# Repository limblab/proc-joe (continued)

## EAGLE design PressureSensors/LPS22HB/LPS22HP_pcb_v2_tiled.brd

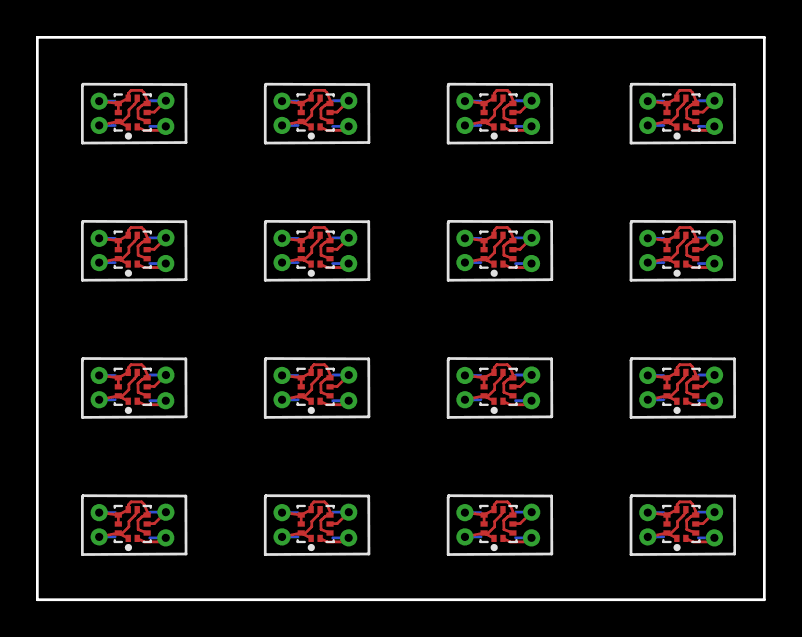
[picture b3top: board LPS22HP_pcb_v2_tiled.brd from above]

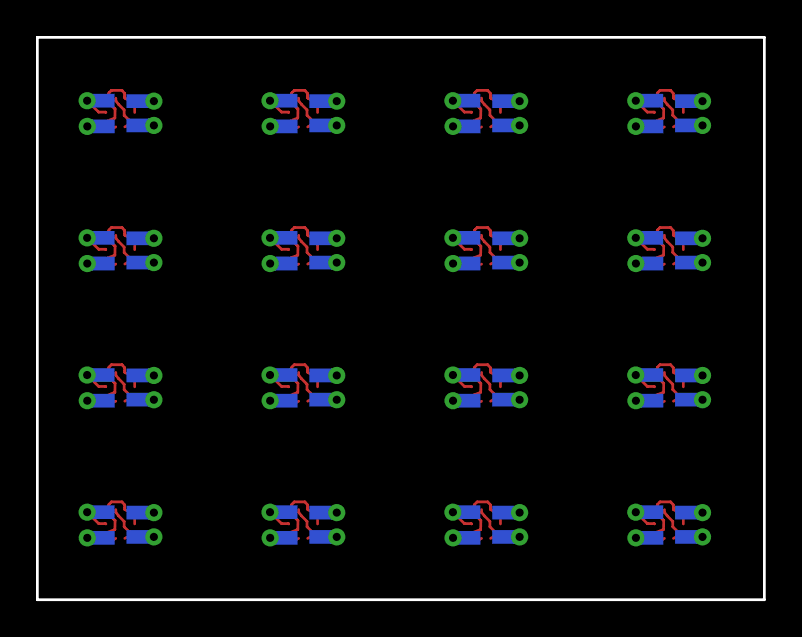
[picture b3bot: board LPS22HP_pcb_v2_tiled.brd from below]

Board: 2 copper layers, 40.4 x 31.2 mm, 80 parts (64 on the bottom side), 64 nets.

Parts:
U1, U2, U3, U4, U5, U6, U7, U8, U9, U10, U11, U12, U13, U14, U15, U16: LPS22HB; LGA10R50P2X3_200X200X80
U$1, U$2, U$3, U$4, U$5, U$6, U$7, U$8, U$9, U$10, U$11, U$12, U$13, U$14, U$15, U$16, U$17, U$18, U$19, U$20, U$21, U$22, U$23, U$24, U$25, U$26, U$27, U$28, U$29, U$30, U$31, U$32, U$33, U$34, U$35, U$36, U$37, U$38, U$39, U$40, U$41, U$42, U$43, U$44, U$45, U$46, U$47, U$48, U$49, U$50, U$51, U$52, U$53, U$54, U$55, U$56, U$57, U$58, U$59, U$60, U$61, U$62, U$63, U$64: WIREPAD_PADWIREPAD_0,6/0,4_PAD; WIREPAD_0,6/0,4_PAD

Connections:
+3V1: U2.1, U2.6, U2.10, U$5.P$1, U$5.P$2
+3V2: U3.1, U3.6, U3.10, U$11.P$1, U$11.P$2
+3V3: U1.1, U1.6, U1.10, U$1.P$1, U$1.P$2
+3V4: U4.1, U4.6, U4.10, U$15.P$1, U$15.P$2
+3V5: U5.1, U5.6, U5.10, U$19.P$1, U$19.P$2
+3V6: U6.1, U6.6, U6.10, U$23.P$1, U$23.P$2
+3V7: U7.1, U7.6, U7.10, U$27.P$1, U$27.P$2
+3V8: U8.1, U8.6, U8.10, U$31.P$1, U$31.P$2
+3V9: U9.1, U9.6, U9.10, U$35.P$1, U$35.P$2
+3V10: U10.1, U10.6, U10.10, U$39.P$1, U$39.P$2
+3V11: U11.1, U11.6, U11.10, U$43.P$1, U$43.P$2
+3V12: U12.1, U12.6, U12.10, U$47.P$1, U$47.P$2
+3V13: U13.1, U13.6, U13.10, U$51.P$1, U$51.P$2
+3V14: U14.1, U14.6, U14.10, U$55.P$1, U$55.P$2
+3V15: U15.1, U15.6, U15.10, U$59.P$1, U$59.P$2
+3V16: U16.1, U16.6, U16.10, U$63.P$1, U$63.P$2
GND: U1.3, U1.5, U1.7, U1.8, U1.9, U$2.P$1, U$2.P$2
GND1: U2.3, U2.5, U2.7, U2.8, U2.9, U$8.P$1, U$8.P$2
GND2: U3.3, U3.5, U3.7, U3.8, U3.9, U$12.P$1, U$12.P$2
GND3: U4.3, U4.5, U4.7, U4.8, U4.9, U$16.P$1, U$16.P$2
GND4: U5.3, U5.5, U5.7, U5.8, U5.9, U$20.P$1, U$20.P$2
GND5: U6.3, U6.5, U6.7, U6.8, U6.9, U$24.P$1, U$24.P$2
GND6: U7.3, U7.5, U7.7, U7.8, U7.9, U$28.P$1, U$28.P$2
GND7: U8.3, U8.5, U8.7, U8.8, U8.9, U$32.P$1, U$32.P$2
GND8: U9.3, U9.5, U9.7, U9.8, U9.9, U$36.P$1, U$36.P$2
GND9: U10.3, U10.5, U10.7, U10.8, U10.9, U$40.P$1, U$40.P$2
GND10: U11.3, U11.5, U11.7, U11.8, U11.9, U$44.P$1, U$44.P$2
GND11: U12.3, U12.5, U12.7, U12.8, U12.9, U$48.P$1, U$48.P$2
GND12: U13.3, U13.5, U13.7, U13.8, U13.9, U$52.P$1, U$52.P$2
GND13: U14.3, U14.5, U14.7, U14.8, U14.9, U$56.P$1, U$56.P$2
GND14: U15.3, U15.5, U15.7, U15.8, U15.9, U$60.P$1, U$60.P$2
GND15: U16.3, U16.5, U16.7, U16.8, U16.9, U$64.P$1, U$64.P$2
unnamed: U2.2, U$3.P$1, U$3.P$2
unnamed: U1.2, U$6.P$1, U$6.P$2
unnamed: U1.4, U$7.P$1, U$7.P$2
unnamed: U2.4, U$4.P$1, U$4.P$2
unnamed: U3.2, U$9.P$1, U$9.P$2
unnamed: U3.4, U$10.P$1, U$10.P$2
unnamed: U4.2, U$13.P$1, U$13.P$2
unnamed: U4.4, U$14.P$1, U$14.P$2
unnamed: U5.2, U$17.P$1, U$17.P$2
unnamed: U5.4, U$18.P$1, U$18.P$2
unnamed: U6.2, U$21.P$1, U$21.P$2
unnamed: U6.4, U$22.P$1, U$22.P$2
unnamed: U7.2, U$25.P$1, U$25.P$2
unnamed: U7.4, U$26.P$1, U$26.P$2
unnamed: U8.2, U$29.P$1, U$29.P$2
unnamed: U8.4, U$30.P$1, U$30.P$2
unnamed: U9.2, U$33.P$1, U$33.P$2
unnamed: U9.4, U$34.P$1, U$34.P$2
unnamed: U10.2, U$37.P$1, U$37.P$2
unnamed: U10.4, U$38.P$1, U$38.P$2
unnamed: U11.2, U$41.P$1, U$41.P$2
unnamed: U11.4, U$42.P$1, U$42.P$2
unnamed: U12.2, U$45.P$1, U$45.P$2
unnamed: U12.4, U$46.P$1, U$46.P$2
unnamed: U13.2, U$49.P$1, U$49.P$2
unnamed: U13.4, U$50.P$1, U$50.P$2
unnamed: U14.2, U$53.P$1, U$53.P$2
unnamed: U14.4, U$54.P$1, U$54.P$2
unnamed: U15.2, U$57.P$1, U$57.P$2
unnamed: U15.4, U$58.P$1, U$58.P$2
unnamed: U16.2, U$61.P$1, U$61.P$2
unnamed: U16.4, U$62.P$1, U$62.P$2

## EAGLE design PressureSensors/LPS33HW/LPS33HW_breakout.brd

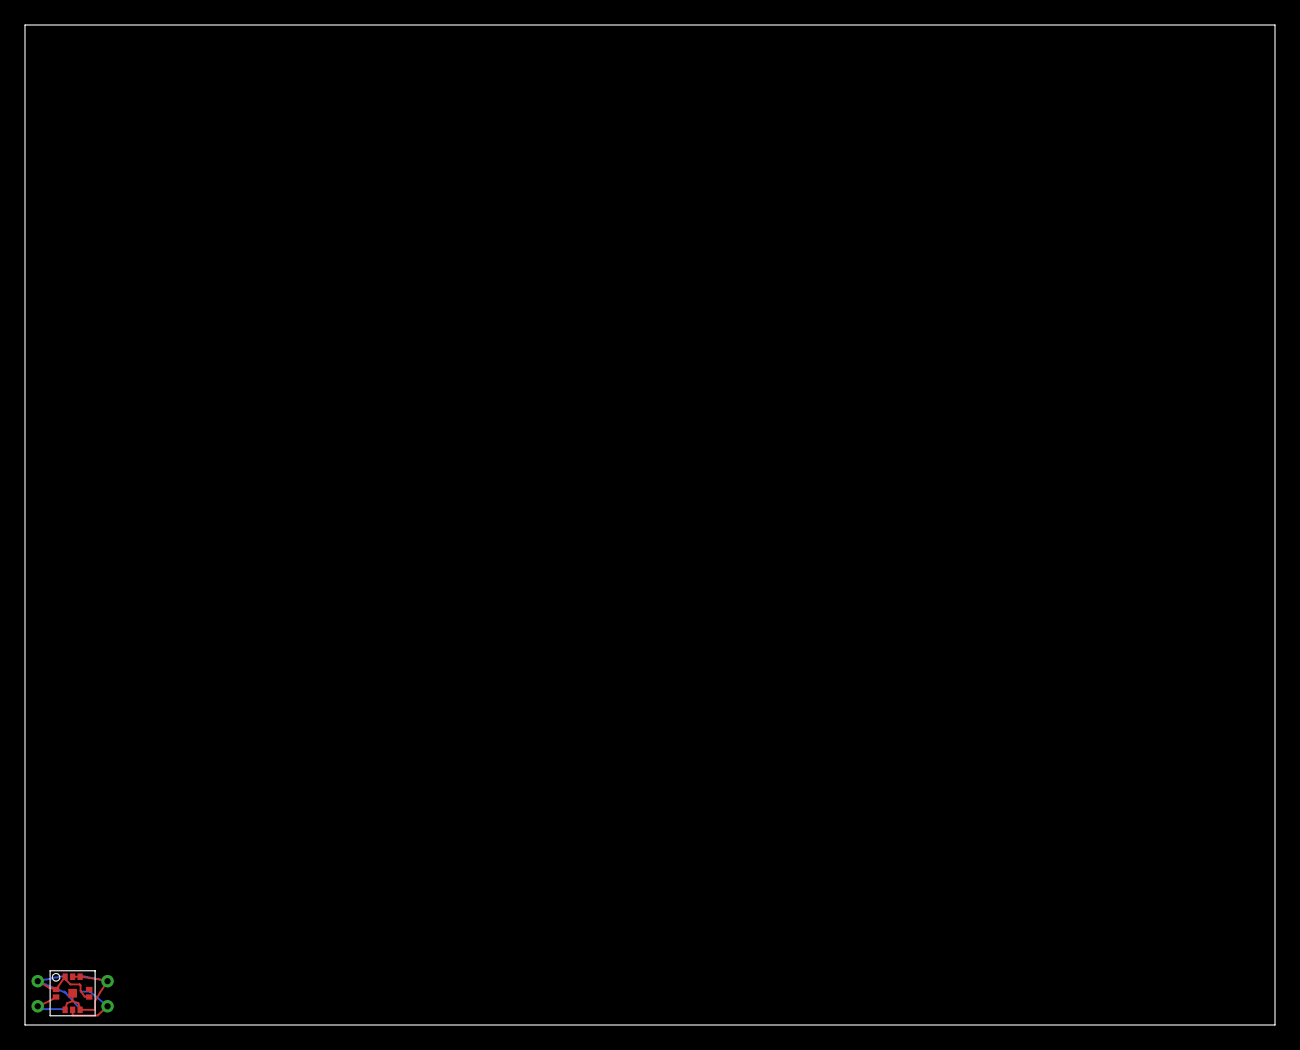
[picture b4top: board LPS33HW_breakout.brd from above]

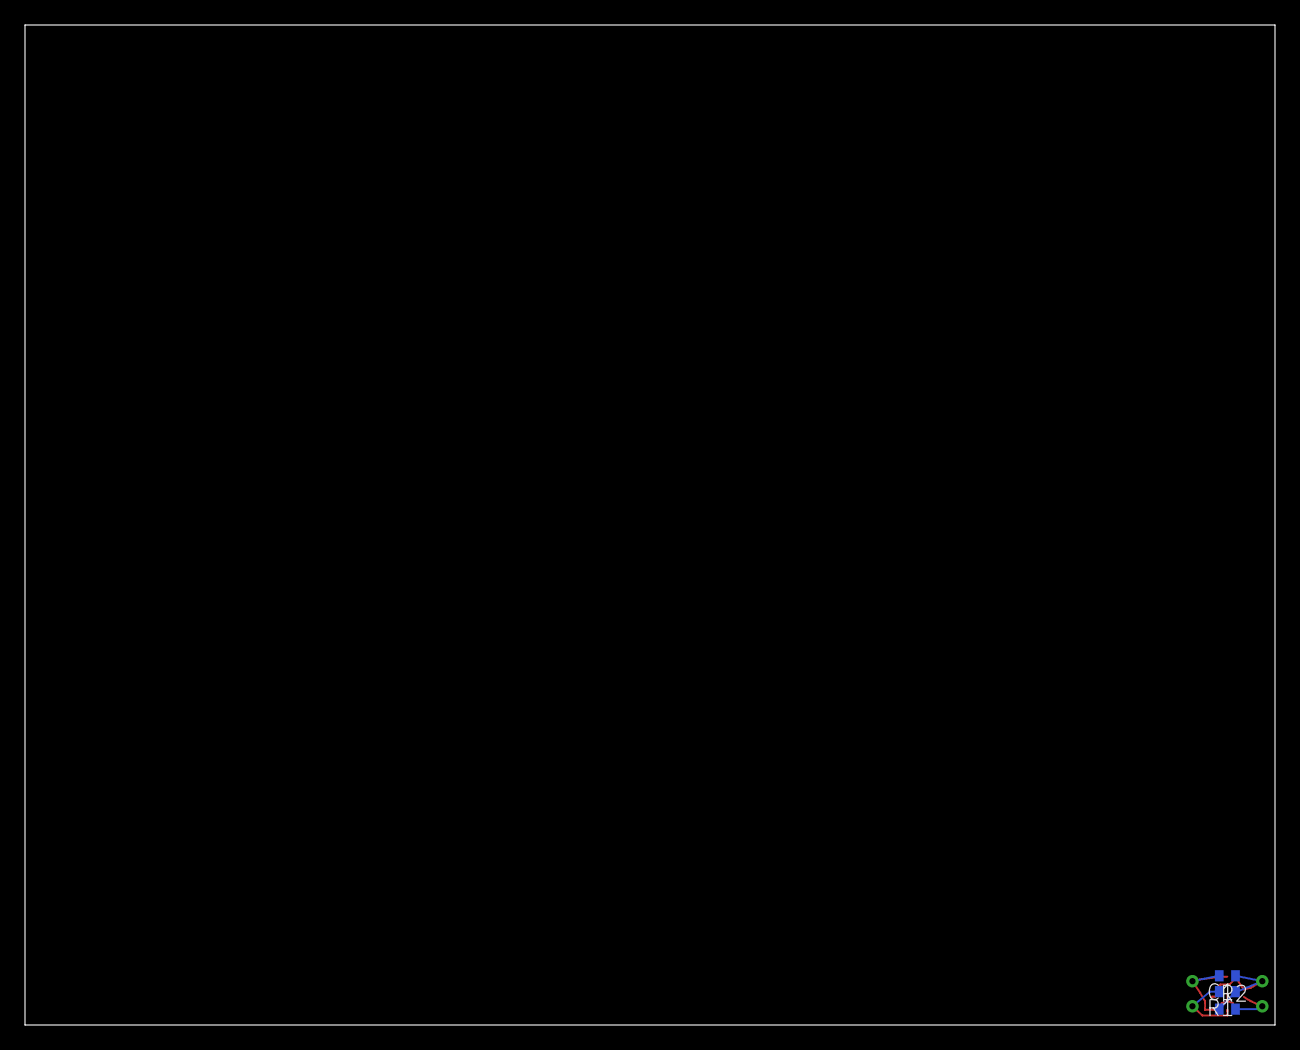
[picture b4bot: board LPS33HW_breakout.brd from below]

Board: 2 copper layers, 100.0 x 80.0 mm, 8 parts (3 on the bottom side), 4 nets.

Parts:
C1: C0402
R1, R2: R0402
U$1: LPS33HW
U$2, U$3, U$4, U$5: VIA

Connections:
+3V3: C1.1, R1.1, R2.1, U$1.P$1, U$1.P$6, U$1.P$10, U$2.P$1
GND: C1.2, U$1.GND, U$1.P$3, U$1.P$5, U$1.P$8, U$1.P$9, U$3.P$1
unnamed: R2.2, U$1.P$2, U$5.P$1
unnamed: R1.2, U$1.P$4, U$4.P$1

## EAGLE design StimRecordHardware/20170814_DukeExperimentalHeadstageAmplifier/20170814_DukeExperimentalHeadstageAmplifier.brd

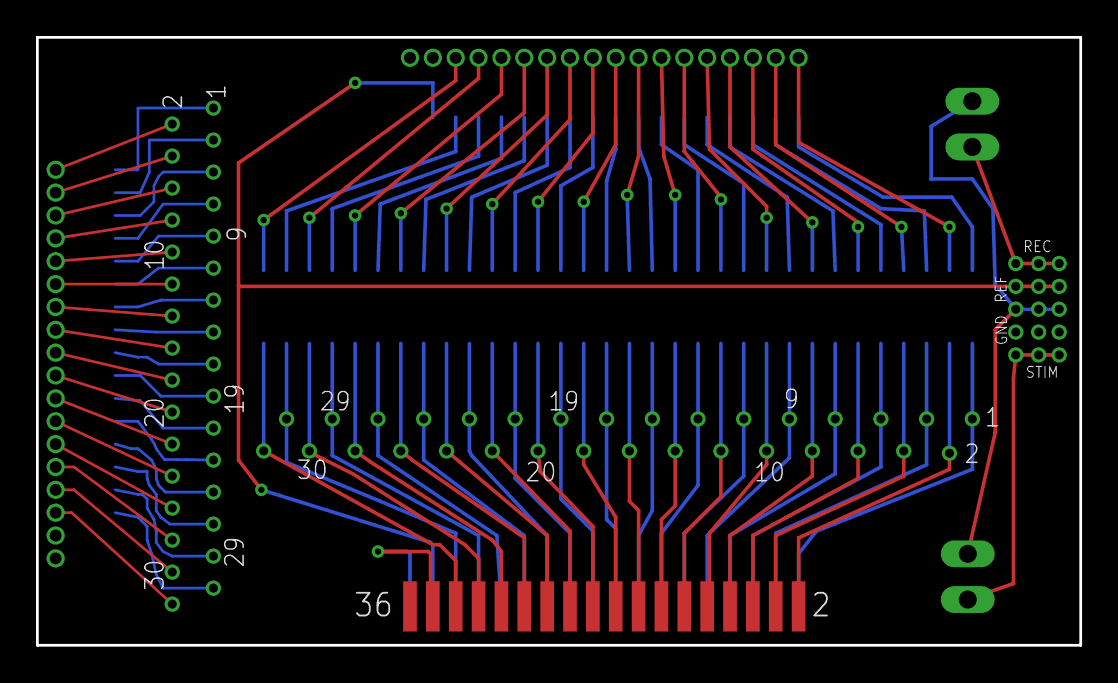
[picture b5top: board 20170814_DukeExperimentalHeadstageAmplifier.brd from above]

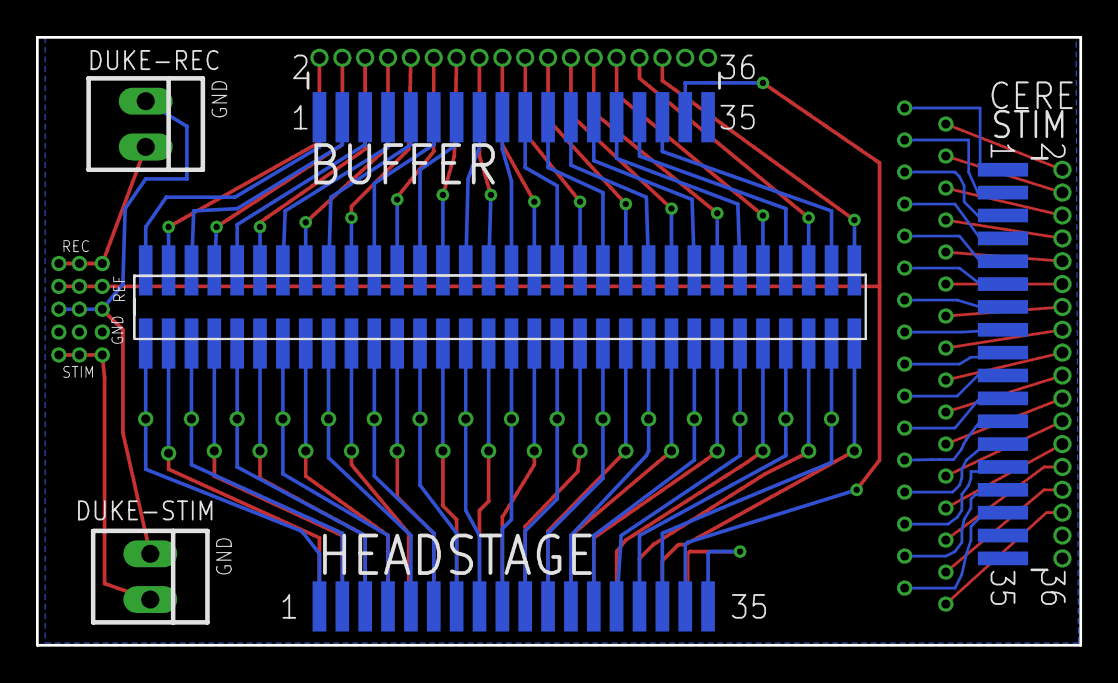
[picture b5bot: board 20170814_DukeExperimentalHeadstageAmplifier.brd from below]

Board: 2 copper layers, 58.0 x 33.8 mm, 41 parts (7 on the bottom side), 101 nets.

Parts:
BUFFER: FTSH-118-01-L-MTREGULAR; FTSH-118-01-L-MT
DUKE-REC: 22-23-2021
DUKE-STIM: 22-23-2021
HEADSTAGE: SFMC-118-L1-S-D
STIM: FTSH-118-01-L-MTREGULAR; FTSH-118-01-L-MT
U$1, U$2, U$4, U$5, U$6, U$7, U$8, U$9, U$10, U$11, U$12, U$13, U$14, U$15, U$16, U$17, U$18, U$19, U$20, U$21, U$22, U$23, U$24, U$25, U$26, U$27, U$28, U$29, U$30, U$31, U$32, U$33: VIA
U$3: FTSH-132-01-L-DV; FTSH-132-01-DV
U$34, U$35, U$36: LPPB051NFFN-RC

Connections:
0V: BUFFER.33, HEADSTAGE.33, U$34.P$2, U$35.P$2, U$36.P$2
GND: BUFFER.34, BUFFER.35, HEADSTAGE.34, HEADSTAGE.35, STIM.34, STIM.35, U$34.P$4, U$35.P$4, U$36.P$4
unnamed: BUFFER.1, U$3.2
unnamed: BUFFER.29, U$3.58
unnamed: BUFFER.3, U$3.6
unnamed: BUFFER.2, U$3.4
unnamed: BUFFER.5, U$3.10
unnamed: BUFFER.7, U$3.14
unnamed: BUFFER.9, U$3.18
unnamed: BUFFER.11, U$3.22
unnamed: BUFFER.13, U$3.26
unnamed: BUFFER.15, U$3.30
unnamed: BUFFER.17, U$3.34
unnamed: BUFFER.19, U$3.38
unnamed: BUFFER.27, U$3.54
unnamed: BUFFER.23, U$3.46
unnamed: BUFFER.25, U$3.50
unnamed: BUFFER.4, U$3.8
unnamed: BUFFER.6, U$3.12
unnamed: BUFFER.31, U$3.62
unnamed: BUFFER.8, U$3.16
unnamed: BUFFER.10, U$3.20
unnamed: BUFFER.12, U$3.24
unnamed: BUFFER.14, U$3.28
unnamed: BUFFER.16, U$3.32
unnamed: BUFFER.18, U$3.36
unnamed: BUFFER.20, U$3.40
unnamed: BUFFER.21, U$3.42
unnamed: BUFFER.22, U$3.44
unnamed: BUFFER.24, U$3.48
unnamed: BUFFER.26, U$3.52
unnamed: BUFFER.28, U$3.56
unnamed: BUFFER.30, U$3.60
unnamed: BUFFER.32, U$3.64
unnamed: HEADSTAGE.1, U$3.1
unnamed: HEADSTAGE.3, U$3.5
unnamed: HEADSTAGE.5, U$3.9
unnamed: HEADSTAGE.7, U$3.13
unnamed: HEADSTAGE.9, U$3.17
unnamed: HEADSTAGE.11, U$3.21
unnamed: HEADSTAGE.13, U$3.25
unnamed: HEADSTAGE.15, U$3.29
unnamed: HEADSTAGE.17, U$3.33
unnamed: HEADSTAGE.19, U$3.37
unnamed: HEADSTAGE.21, U$3.41
unnamed: HEADSTAGE.23, U$3.45
unnamed: HEADSTAGE.25, U$3.49
unnamed: HEADSTAGE.27, U$3.53
unnamed: HEADSTAGE.29, U$3.57
unnamed: HEADSTAGE.31, U$3.61
unnamed: HEADSTAGE.2, U$3.3
unnamed: HEADSTAGE.4, U$3.7
unnamed: HEADSTAGE.6, U$3.11
unnamed: HEADSTAGE.8, U$3.15
unnamed: HEADSTAGE.10, U$3.19
unnamed: HEADSTAGE.12, U$3.23
unnamed: HEADSTAGE.14, U$3.27
unnamed: HEADSTAGE.16, U$3.31
unnamed: HEADSTAGE.18, U$3.35
unnamed: HEADSTAGE.20, U$3.39
unnamed: HEADSTAGE.22, U$3.43
unnamed: HEADSTAGE.24, U$3.47
unnamed: HEADSTAGE.26, U$3.51
unnamed: HEADSTAGE.28, U$3.55
unnamed: HEADSTAGE.30, U$3.59
unnamed: HEADSTAGE.32, U$3.63
unnamed: STIM.1, U$33.P$1
unnamed: STIM.3, U$32.P$1
unnamed: STIM.5, U$31.P$1
unnamed: STIM.7, U$30.P$1
unnamed: STIM.9, U$29.P$1
unnamed: STIM.11, U$28.P$1
unnamed: STIM.13, U$27.P$1
unnamed: STIM.15, U$26.P$1
unnamed: STIM.17, U$25.P$1
unnamed: STIM.19, U$24.P$1
unnamed: STIM.21, U$23.P$1
unnamed: STIM.23, U$22.P$1
unnamed: STIM.25, U$21.P$1
unnamed: STIM.27, U$20.P$1
unnamed: STIM.29, U$19.P$1
unnamed: STIM.31, U$18.P$1
unnamed: STIM.32, U$17.P$1
unnamed: STIM.30, U$16.P$1
unnamed: STIM.28, U$15.P$1
unnamed: STIM.26, U$14.P$1
unnamed: STIM.24, U$13.P$1
unnamed: STIM.22, U$12.P$1
unnamed: STIM.20, U$11.P$1
unnamed: STIM.18, U$10.P$1
unnamed: STIM.16, U$9.P$1
unnamed: STIM.14, U$8.P$1
unnamed: STIM.12, U$7.P$1
unnamed: STIM.10, U$6.P$1
unnamed: STIM.8, U$5.P$1
unnamed: STIM.6, U$4.P$1
unnamed: STIM.4, U$2.P$1
unnamed: STIM.2, U$1.P$1
unnamed: DUKE-REC.1, DUKE-STIM.1, U$34.P$3, U$35.P$3, U$36.P$3
unnamed: DUKE-REC.2, U$34.P$1, U$35.P$1, U$36.P$1
unnamed: DUKE-STIM.2, U$34.P$5, U$35.P$5, U$36.P$5
